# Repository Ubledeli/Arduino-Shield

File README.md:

# Arduino-Shield
A shield for Arduino Leonardo

Supports two RGB LED strips and two mains powered appliances

Powered from 12V source which can also be used for powering the Arduino itself

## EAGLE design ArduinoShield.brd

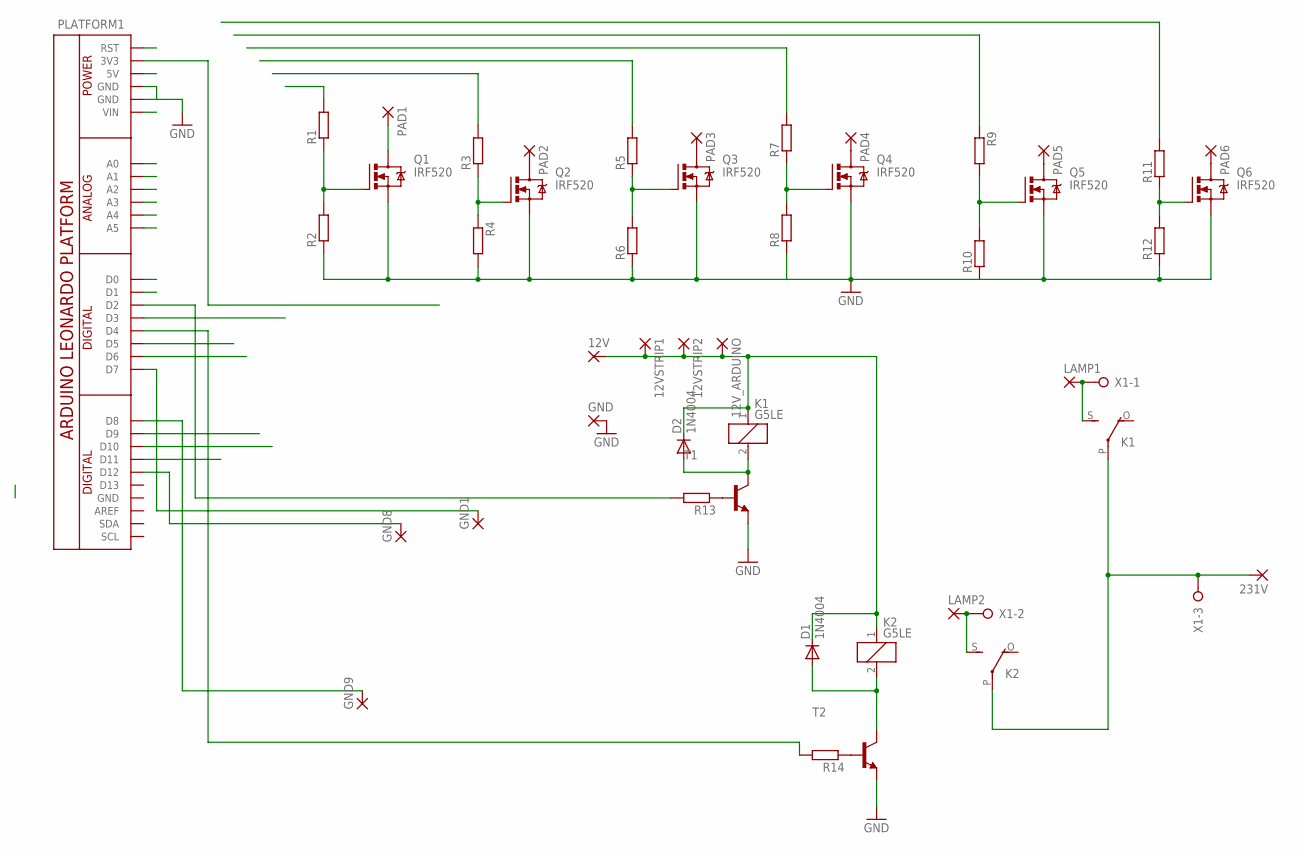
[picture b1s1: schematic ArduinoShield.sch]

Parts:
12V, 12VSTRIP1, 12VSTRIP2, 12V_ARDUINO, 231V: WIREPAD1,6/0,8; 1,6/0,8
D1, D2: 1N4004; DO41-10
GND, GND1, GND8, GND9: WIREPAD1,6/0,8; 1,6/0,8
K1, K2: G5LE
LAMP1, LAMP2: WIREPAD1,6/0,8; 1,6/0,8
PAD1, PAD2, PAD3, PAD4, PAD5, PAD6: WIREPAD1,6/0,8; 1,6/0,8
PLATFORM1: 1xPN1x10+1xPN1x8+2xPN1x6; ARDUINO-LEONARDO-PLATFORM
Q1, Q2, Q3, Q4, Q5, Q6: IRF520; TO220BV
R1, R2, R3, R4, R5, R6, R7, R8, R9, R10, R11, R12, R13, R14: R-EU_0207/7; 0207/7
T1, T2: BC547-NPN-TO92-CBE; TO92-CBE
X1: W237-3E

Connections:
GND: GND.1, PLATFORM1.GND, PLATFORM1.GND@1 (GND), Q1.S, Q2.S, Q3.S, Q4.S, Q5.S, Q6.S, R2.1, R4.2, R6.1, R8.1, R10.1, R12.1, T1.E, T2.E
unnamed: Q5.G, R9.2, R10.2
unnamed: Q6.G, R11.1, R12.2
unnamed: Q4.G, R7.1, R8.2
unnamed: Q3.G, R5.1, R6.2
unnamed: Q2.G, R3.1, R4.1
unnamed: Q1.G, R1.1, R2.2
unnamed: PAD1.1, Q1.D
unnamed: PAD2.1, Q2.D
unnamed: PAD3.1, Q3.D
unnamed: PAD4.1, Q4.D
unnamed: PAD5.1, Q5.D
unnamed: PAD6.1, Q6.D
unnamed: PLATFORM1.D5, R3.2
unnamed: PLATFORM1.D6, R5.2
unnamed: D1.A, K2.2, T2.C
unnamed: PLATFORM1.D2, R13.2
unnamed: 12V.1, 12VSTRIP1.1, 12VSTRIP2.1, 12V_ARDUINO.1, D1.C, D2.C, K1.1, K2.1
unnamed: D2.A, K1.2, T1.C
unnamed: R13.1, T1.B
unnamed: R14.1, T2.B
unnamed: PLATFORM1.D4, R14.2
unnamed: K2.S, LAMP2.1, X1.2
unnamed: K1.S, LAMP1.1, X1.1
unnamed: GND9.1, PLATFORM1.D8
unnamed: GND8.1, PLATFORM1.D12
unnamed: GND1.1, PLATFORM1.D7
unnamed: 231V.1, K1.P, K2.P, X1.3
unnamed: PLATFORM1.D3, R1.2

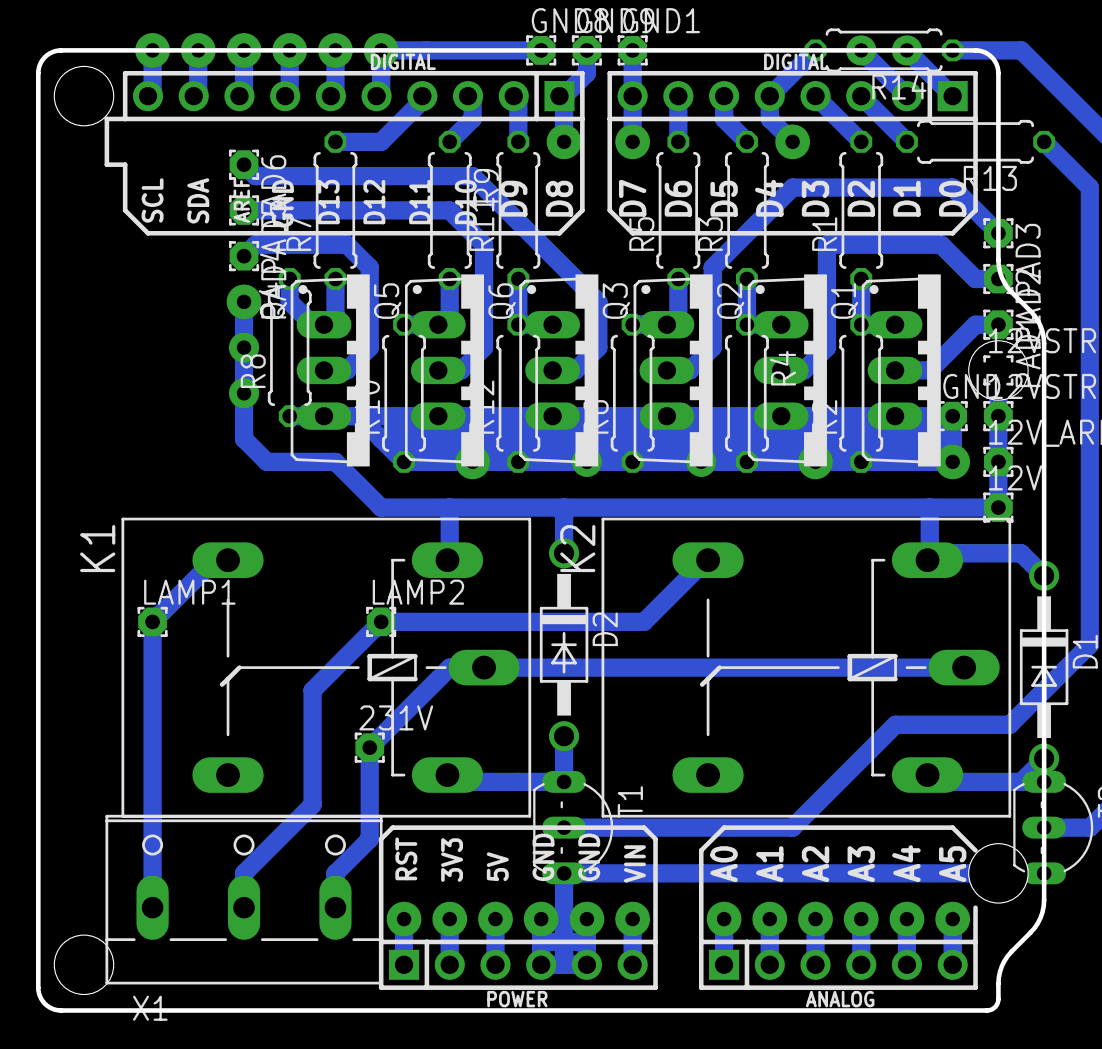
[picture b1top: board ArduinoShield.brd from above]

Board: 2 copper layers, 55.9 x 53.3 mm, 45 parts (0 on the bottom side), 29 nets.

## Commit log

2016-05-08 :lollipop: Added .gitattributes
2016-05-08 Leonardo shield for two RGB_LED strips
    Six MOSFETs on PWM pins for led strips
    Two relays on digital pins
    Exposed connector for BT or WiFi
